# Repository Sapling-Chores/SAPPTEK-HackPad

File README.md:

<div align = "center">

# SAPPTEK-HackPad
### This is a Cyberpunk Themed HackPad Containing 11 programmable keys with cool LEDs and a 0.93 inch oled.

# Why I made this project?
I am a part of The HackClub, and I made this HackPad for the event "BLUEPRINT". And since I am Very big Fan of 'CyberPunk EdgeRunner', I chosed CyberPunk themed HackPad.

# Specification-
* This HackPad uses an small sized XIAO RP2040 DIP Microcontroller to control switches.
* 11 MX style Mechanical Switches.
* 11 RGB LEDs - SK6812-Mini
* A 99x69 PCB
* A 0.91 Inch oled Display
* 3d Printed Case

# Images

## Schematics:

## PCB:

## Case:

# Bom

## 🧾 Bill of Materials (BOM)

| Item                     | Quantity |  Price              |
|--------------------------|----------|----------------------------|
| M2 Screws (10–12 mm)     | As needed| ----    |
| 0.91" OLED Display       | 1        | -----   |
| MX Style Switches        | 11       | ----- |
| SK6812 Mini RGB LEDs     | 11       | ----      |
| 1N4148 Diodes            | 11       | ------  |
| PCB                      | 1        | ~$10.19 USD                |
| 3D Printed Case (Top)    | 1        | ----          |
| 3D Printed Case (Bottom) | 1        | ---           |

Note* I am using   qmk firmware, although I have just started to learn about it.

Note* I will connect the Oled using wire outside the pcb.

## Tools I used :

* Kicad (for pcb and shematics)
* Fusion 360 (for case designing)
* Qmk msys and VS code studio (for firmware.)

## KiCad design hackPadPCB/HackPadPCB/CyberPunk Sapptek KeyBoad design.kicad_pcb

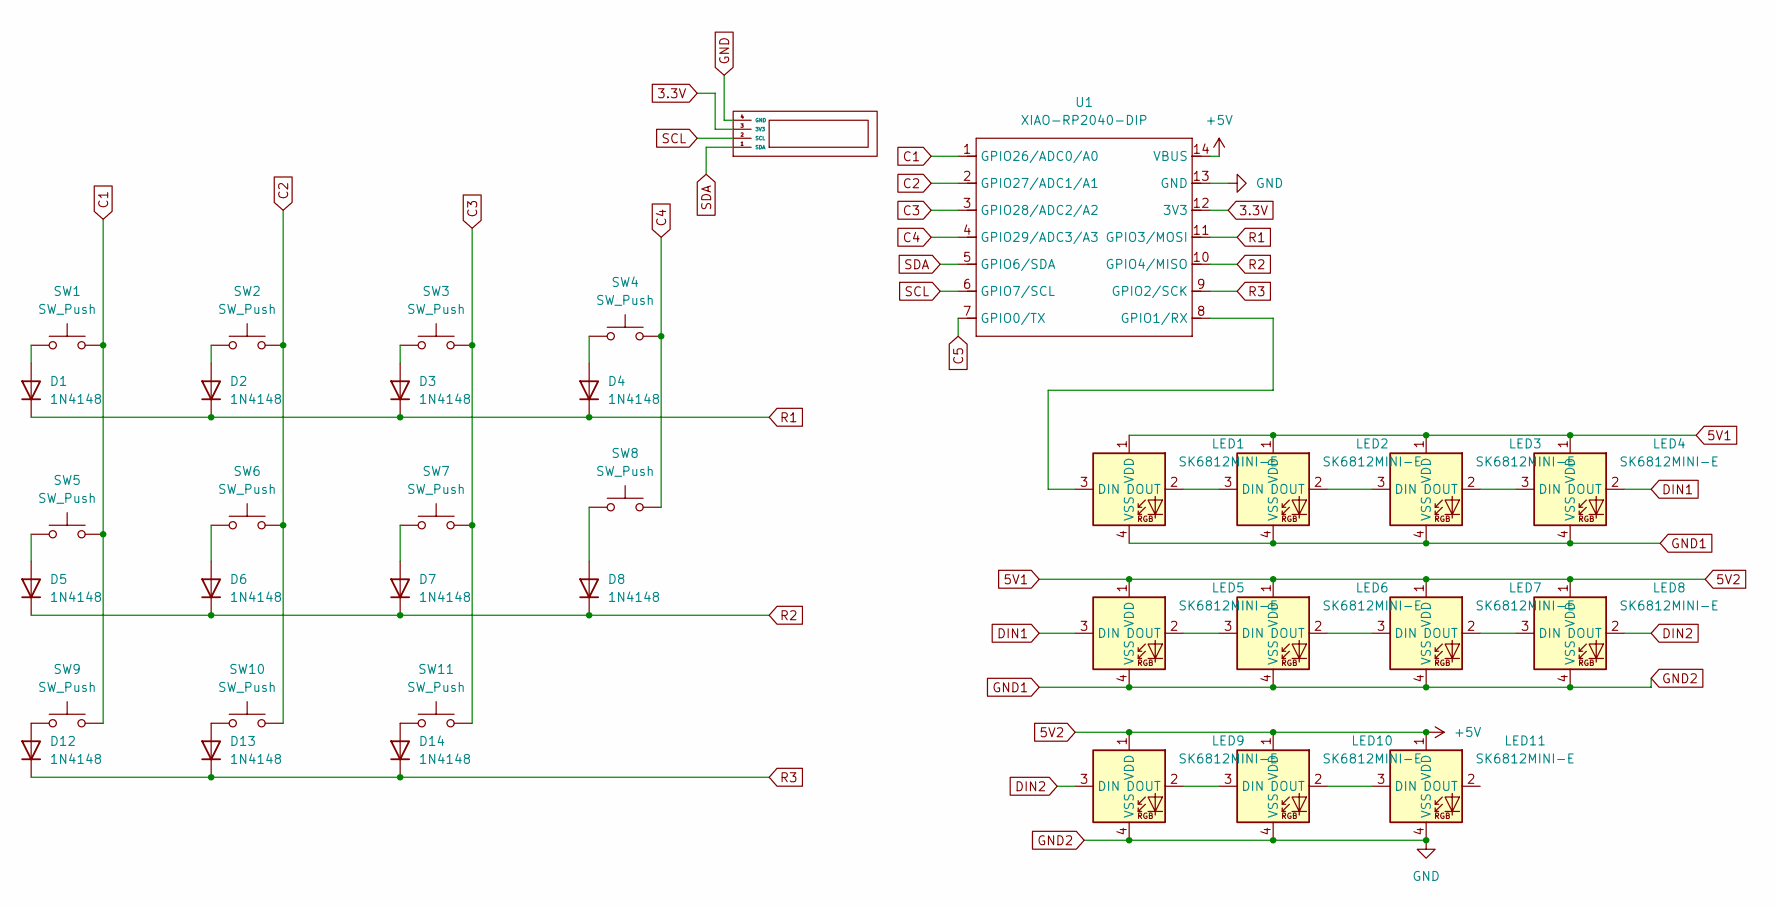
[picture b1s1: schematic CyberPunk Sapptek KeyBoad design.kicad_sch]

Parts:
D1, D2, D3, D4, D5, D6, D7, D8, D12, D13, D14: 1N4148; D_DO-35_SOD27_P7.62mm_Horizontal
LED1, LED2, LED3, LED4, LED5, LED6, LED7, LED8, LED9, LED10, LED11: SK6812MINI-E; MX_SK6812MINI-E_REV
SW1, SW2, SW3, SW4, SW5, SW6, SW7, SW8, SW9, SW10, SW11: SW_Push; SW_Cherry_MX_1.00u_PCB
U1: XIAO-RP2040-DIP; Seeed_XIAO_RP2040
U2: OLED_128x32

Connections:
3.3V: U1.12 (3V3), U2.3 (3V3)
5V1: LED1.1 (VDD), LED2.1 (VDD), LED3.1 (VDD), LED4.1 (VDD), LED5.1 (VDD), LED6.1 (VDD), LED7.1 (VDD), LED8.1 (VDD), LED9.1 (VDD), LED10.1 (VDD), LED11.1 (VDD), U1.14 (VBUS)
C1: SW1.2, SW5.2, SW9.2, U1.1 (GPIO26/ADC0/A0)
C2: SW2.2, SW6.2, SW10.2, U1.2 (GPIO27/ADC1/A1)
C3: SW3.2, SW7.2, SW11.2, U1.3 (GPIO28/ADC2/A2)
C4: SW4.2, SW8.2, U1.4 (GPIO29/ADC3/A3)
C5: U1.7 (GPIO0/TX)
DIN1: LED4.2 (DOUT), LED5.3 (DIN)
DIN2: LED8.2 (DOUT), LED9.3 (DIN)
GND: LED1.4 (VSS), LED2.4 (VSS), LED3.4 (VSS), LED4.4 (VSS), LED5.4 (VSS), LED6.4 (VSS), LED7.4 (VSS), LED8.4 (VSS), LED9.4 (VSS), LED10.4 (VSS), LED11.4 (VSS), U1.13 (GND), U2.4 (GND)
unnamed: D1.2 (A), SW1.1
unnamed: D2.2 (A), SW2.1
unnamed: D3.2 (A), SW3.1
unnamed: D4.2 (A), SW4.1
unnamed: D5.2 (A), SW5.1
unnamed: D6.2 (A), SW6.1
unnamed: D7.2 (A), SW7.1
unnamed: D8.2 (A), SW8.1
unnamed: D12.2 (A), SW9.1
unnamed: D13.2 (A), SW10.1
unnamed: D14.2 (A), SW11.1
unnamed: LED1.3 (DIN), U1.8 (GPIO1/RX)
unnamed: LED1.2 (DOUT), LED2.3 (DIN)
unnamed: LED2.2 (DOUT), LED3.3 (DIN)
unnamed: LED3.2 (DOUT), LED4.3 (DIN)
unnamed: LED5.2 (DOUT), LED6.3 (DIN)
unnamed: LED6.2 (DOUT), LED7.3 (DIN)
unnamed: LED7.2 (DOUT), LED8.3 (DIN)
unnamed: LED9.2 (DOUT), LED10.3 (DIN)
unnamed: LED10.2 (DOUT), LED11.3 (DIN)
R1: D1.1 (K), D2.1 (K), D3.1 (K), D4.1 (K), U1.11 (GPIO3/MOSI)
R2: D5.1 (K), D6.1 (K), D7.1 (K), D8.1 (K), U1.10 (GPIO4/MISO)
R3: D12.1 (K), D13.1 (K), D14.1 (K), U1.9 (GPIO2/SCK)
SCL: U1.6 (GPIO7/SCL), U2.2 (SCL)
SDA: U1.5 (GPIO6/SDA), U2.1 (SDA)

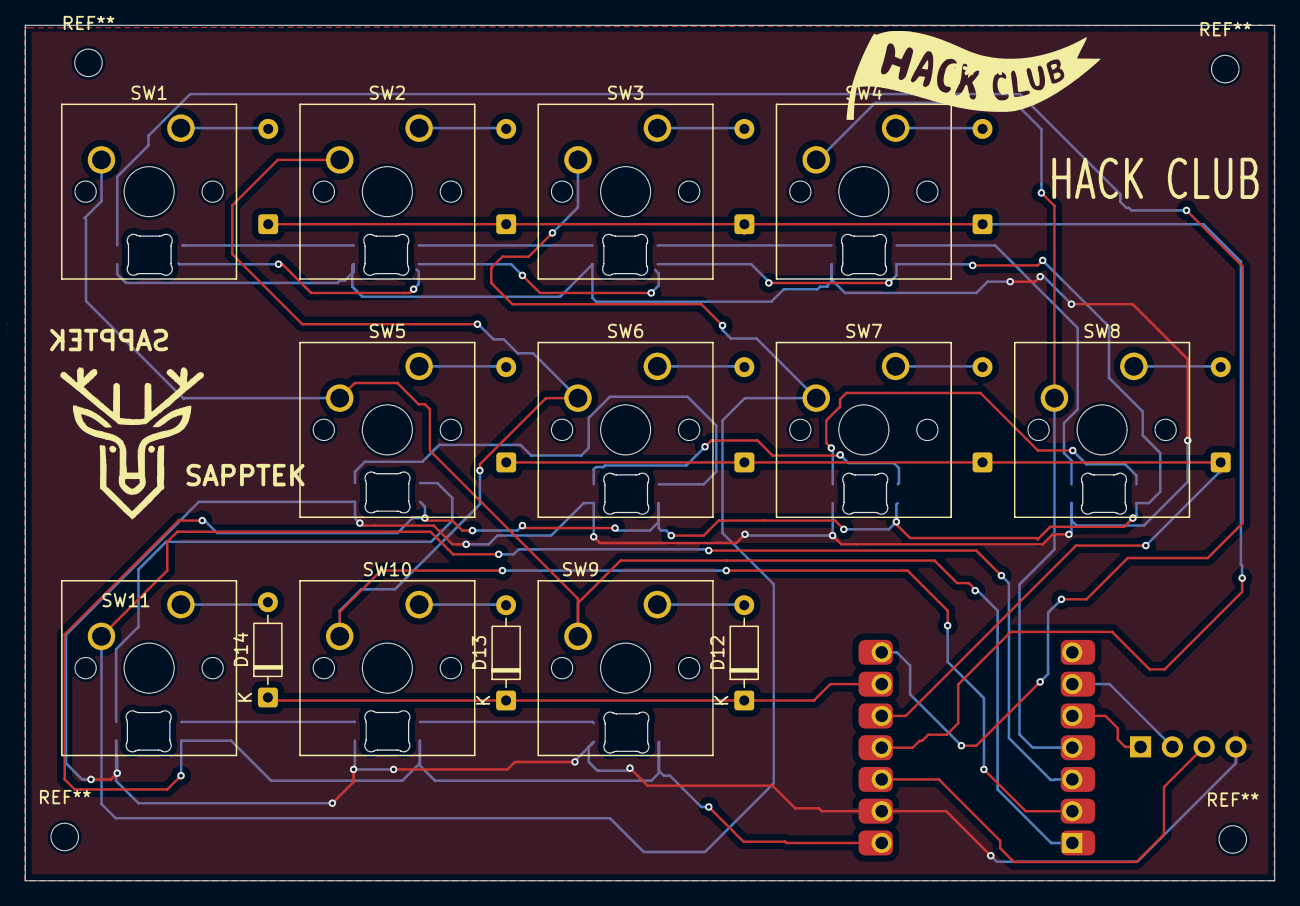
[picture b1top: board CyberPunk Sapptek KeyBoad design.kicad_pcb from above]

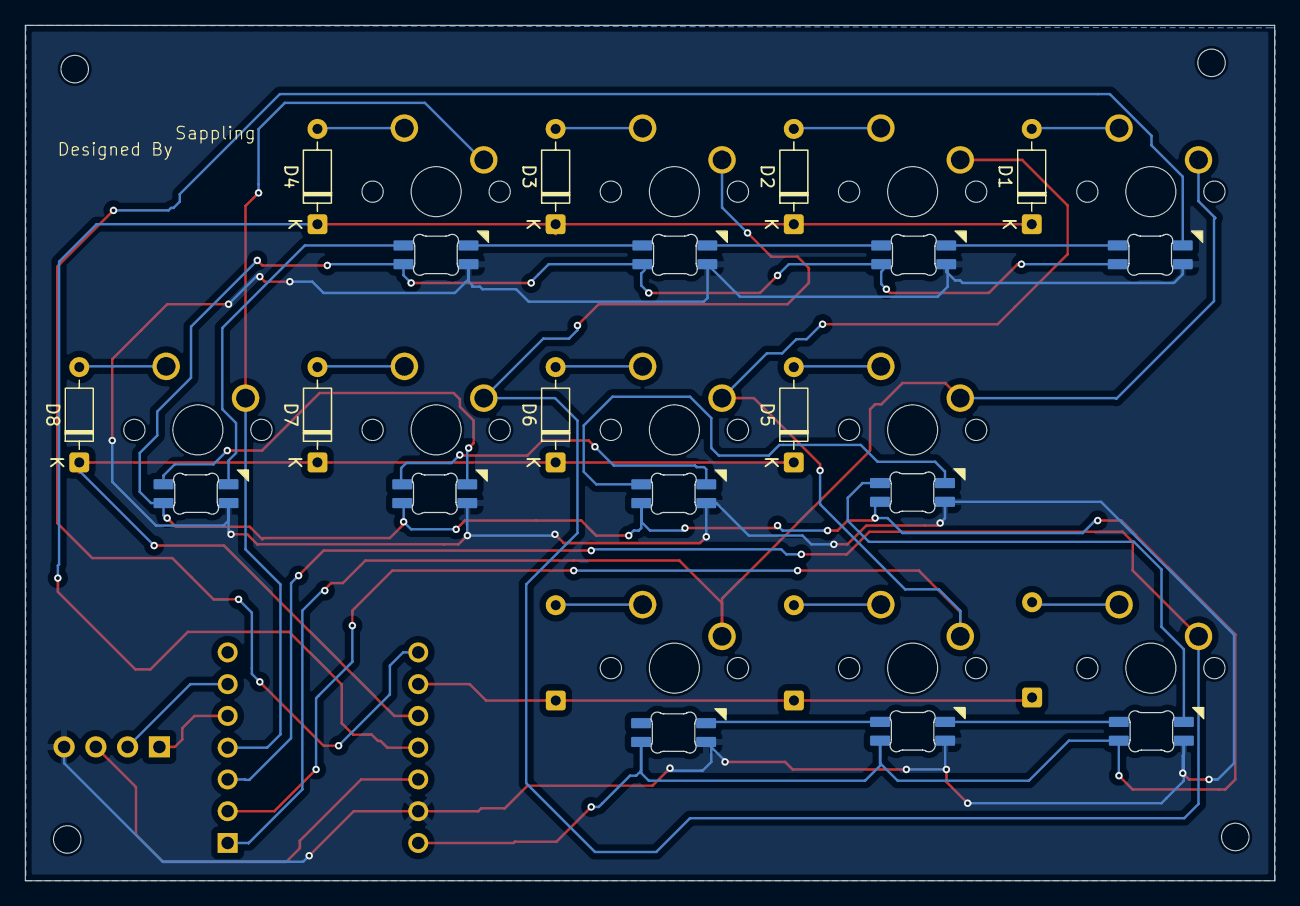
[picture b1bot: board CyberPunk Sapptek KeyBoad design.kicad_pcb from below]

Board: 2 copper layers, 99.9 x 68.4 mm, 35 parts (8 on the bottom side), 34 nets.

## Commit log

2026-01-30 Rename CyberPunk Sapptek KeyBoad design-.zip to HackPadPCB-.zip
2026-03-27 added build image in assets and updated readme.md
2026-06-24 Embed YouTube video in README
    Added an embedded YouTube video to showcase the project.
2026-06-24 Remove YouTube embed from README
    Removed YouTube embed iframe from README.
